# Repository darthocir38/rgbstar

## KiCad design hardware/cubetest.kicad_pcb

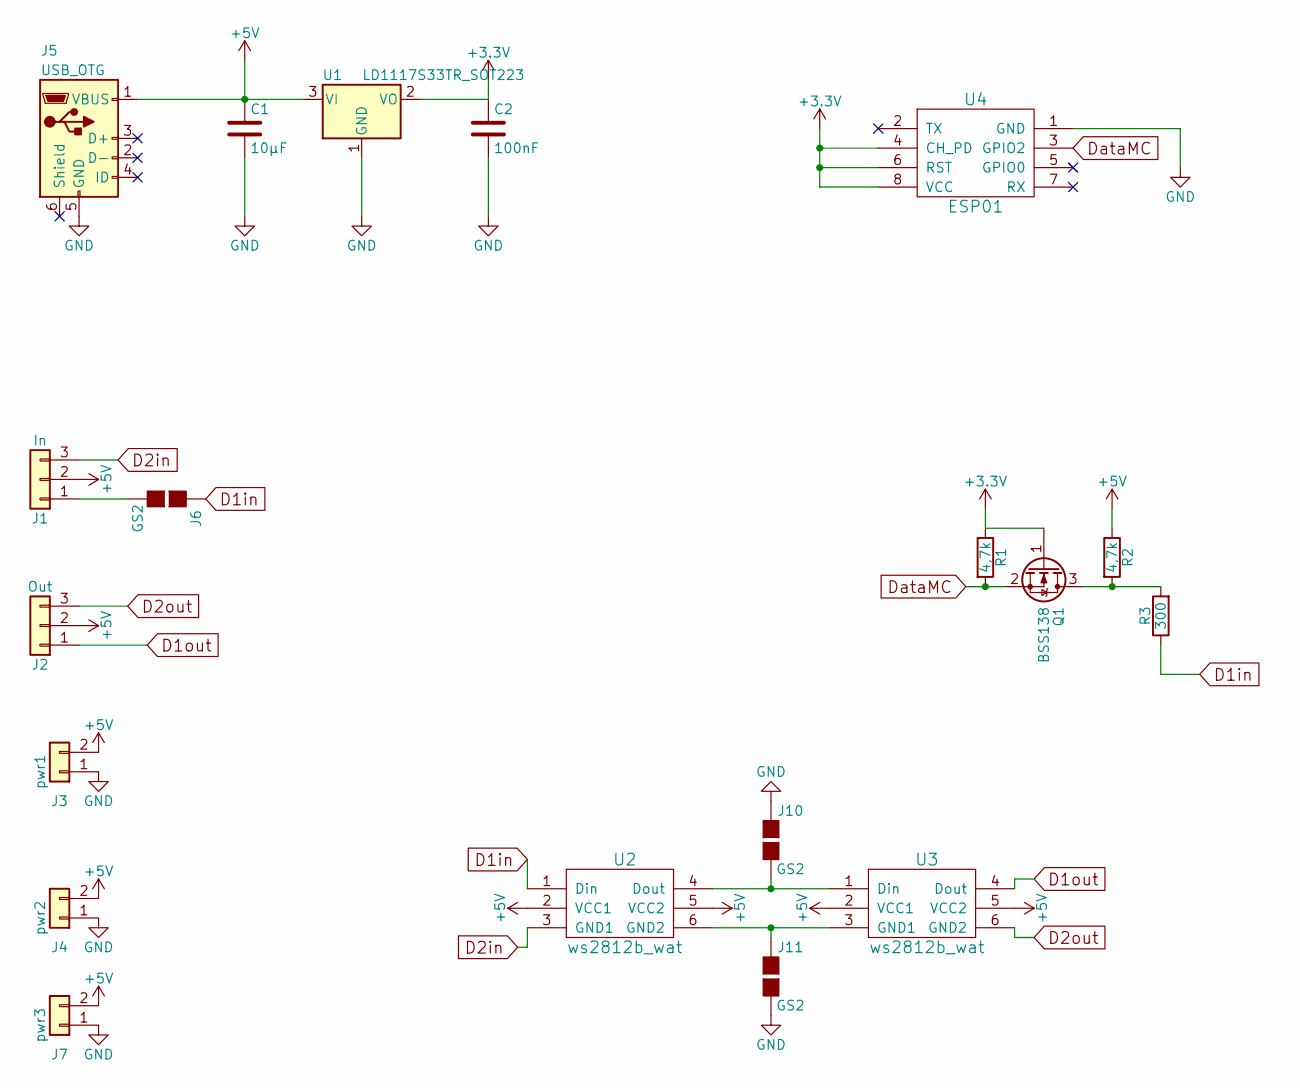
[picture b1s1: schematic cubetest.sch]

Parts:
C1: 10µF; C_1206_HandSoldering
C2: 100nF; C_1206_HandSoldering
J1: In; Pin_Header_Straight_1x03_Pitch2.54mm
J2: Out; Pin_Header_Straight_1x03_Pitch2.54mm
J3: pwr1; Pin_Header_Straight_1x02_Pitch2.54mm
J4: pwr2; Pin_Header_Straight_1x02_Pitch2.54mm
J5: USB_OTG; USB_Micro-B_10103594-0001LF
J6, J10, J11: GS2
J7: pwr3; Pin_Header_Straight_1x02_Pitch2.54mm
Q1: BSS138; SOT-23
R1, R2: 4,7k; R_1206_HandSoldering
R3: 300; R_1206_HandSoldering
U1: LD1117S33TR_SOT223; SOT-223-3Lead_TabPin2
U2, U3: ws2812b_wat; ws2812stri
U4: ESP01; Pin_Header_Angled_2x04_Pitch2.54mm

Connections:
+3V3: C2.1, Q1.1 (G), R1.1, U1.2 (VO), U4.4 (CH_PD), U4.6 (RST), U4.8 (VCC)
+5V: C1.1, J1.2, J2.2, J3.2, J4.2, J5.1 (VBUS), J7.2, R2.1, U1.3 (VI), U2.2 (VCC1), U2.5 (VCC2), U3.2 (VCC1), U3.5 (VCC2)
D1in: J6.1 (G1), R3.1, U2.1 (Din)
D1out: J2.1, U3.4 (Dout)
D2in: J1.3, U2.3 (GND1)
D2out: J2.3, U3.6 (GND2)
DataMC: Q1.2 (S), R1.2, U4.3 (GPIO2)
GND: C1.2, C2.2, J3.1, J4.1, J5.5 (GND), J7.1, J10.1 (G1), J11.2 (G2), U1.1 (GND), U4.1 (GND)
unnamed: J1.1, J6.2 (G2)
unnamed: J10.2 (G2), U2.4 (Dout), U3.1 (Din)
unnamed: J11.1 (G1), U2.6 (GND2), U3.3 (GND1)
unnamed: Q1.3 (D), R2.2, R3.2

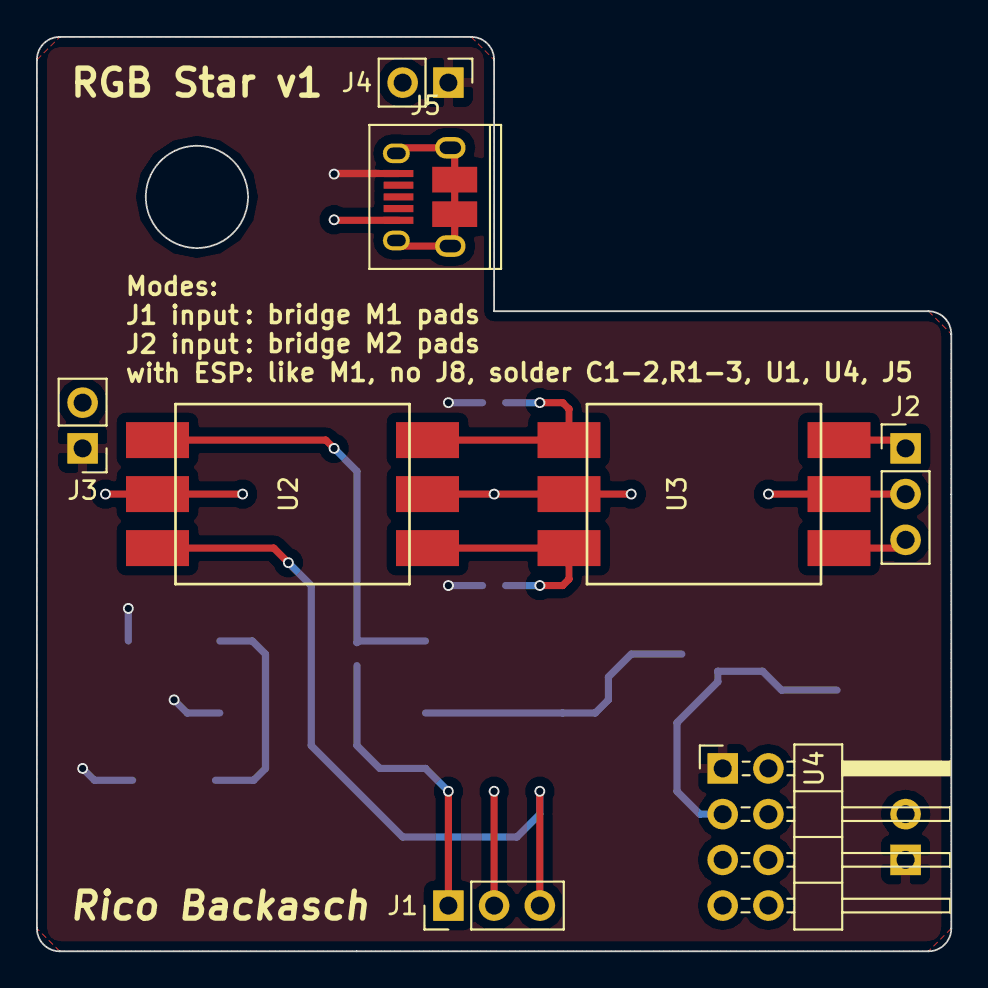
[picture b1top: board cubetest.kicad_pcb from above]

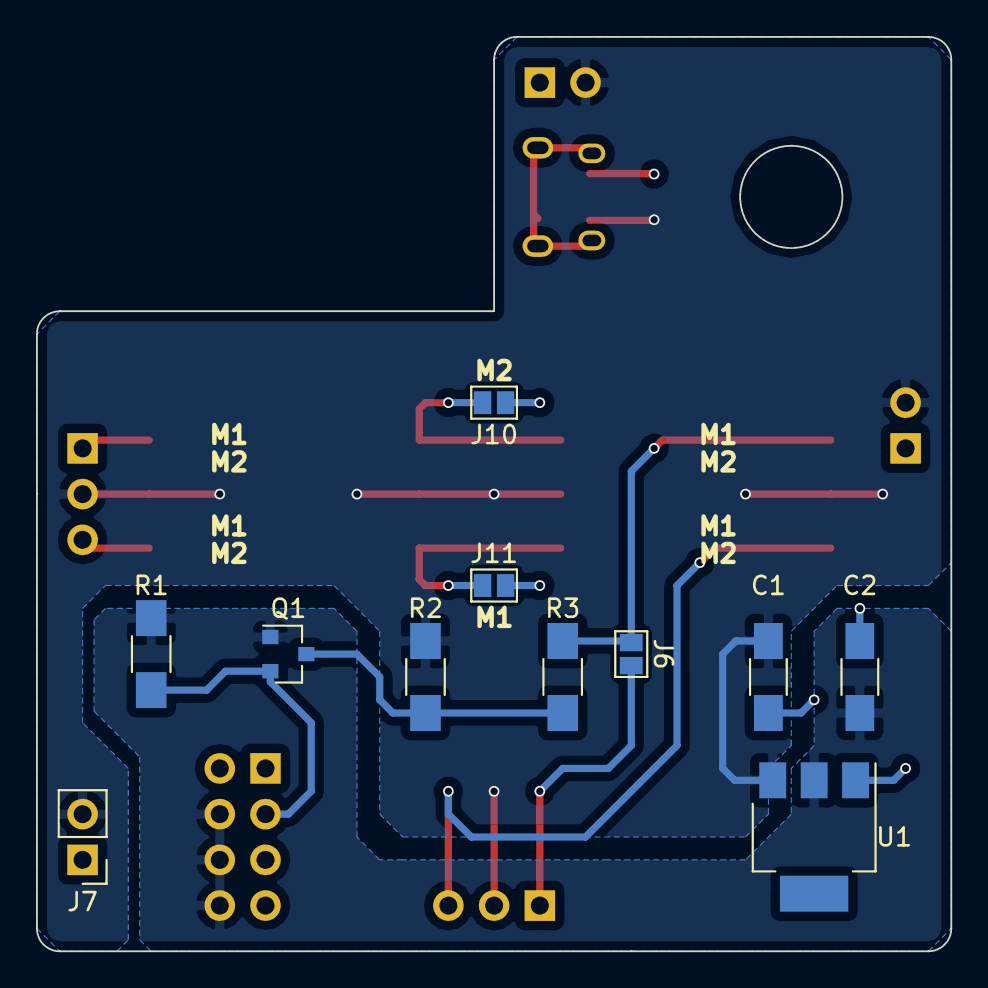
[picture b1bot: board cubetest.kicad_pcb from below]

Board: 2 copper layers, 50.8 x 50.8 mm, 19 parts (11 on the bottom side), 12 nets.

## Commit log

2017-12-24 PlatformIO Template
2017-12-24 Add ESPManager and FastLED
2017-12-24 restructure into software directory
2017-12-24 First kicad files
2017-12-25 Added own hw-libs
2017-12-25 remove solder bridges
2017-12-26 fix pcb, added new pwr
